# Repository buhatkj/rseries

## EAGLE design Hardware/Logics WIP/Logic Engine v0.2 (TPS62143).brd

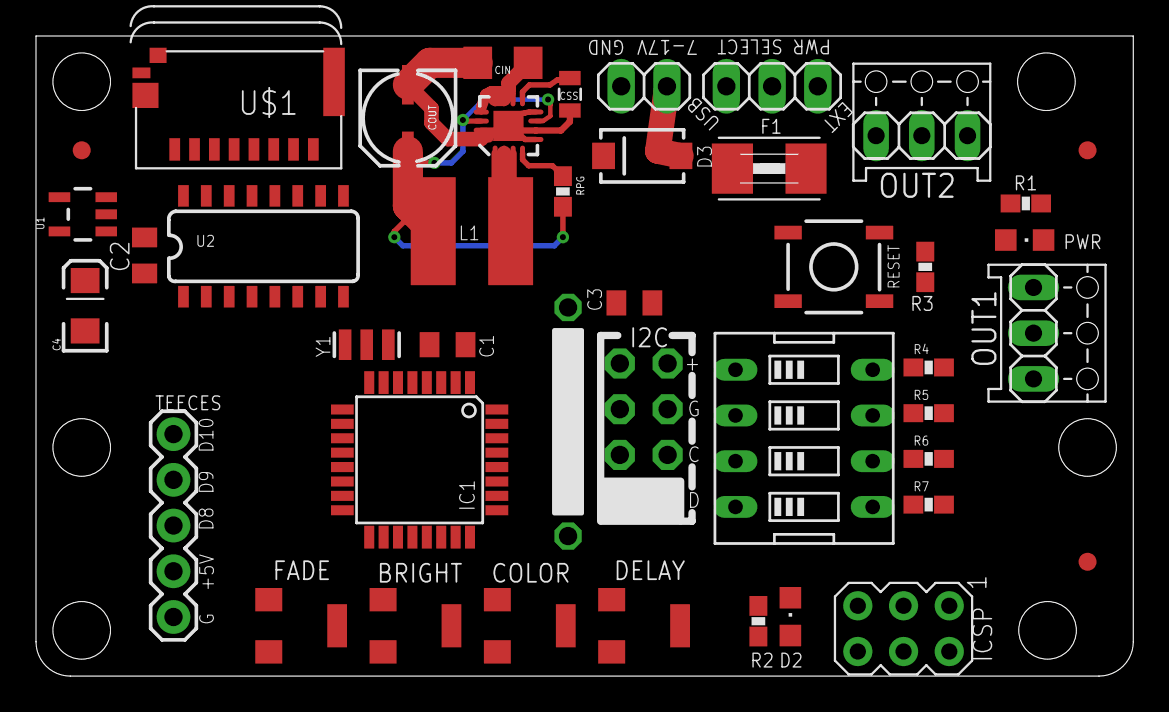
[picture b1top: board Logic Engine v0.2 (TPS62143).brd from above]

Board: 2 copper layers, 61.0 x 35.6 mm, 44 parts (0 on the bottom side), 44 nets.

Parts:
BRIGHT: 3364
C1, C2, C3: 0.1uF; C0805K
C4: 10uF; EIA3216
CIN: 1206
COLOR: 3364
COUT: PANASONIC_C
CSS: 0805
D2: CHIPLED_0805
D3: BA340LA; SMA-DIODE
DELAY: 3364
EXT_PWR: 1X02
F1: 1812
FADE: 3364
FID1, FID2, FID3: FIDUCIAL1X2.5; FIDUCIAL-1X2.5
FTDI: GRN TX RX 5V G BLK; 1X06-CLEAN
I2C, I2C1: 1X04-CB
IC1: MEGA328P; TQFP32-08
ICSP: AVRISP-6; AVRISP
L1: 33uH; SRN6045
OUT1, OUT2: MDF7_1X03
PWR: CHIPLED_0805
PWR_SEL1: 1X03
R1, R2: 1K; 0603-RES
R3, R4, R5, R6, R7: 10K; 0603-RES
RESET: TACTILE_SWITCH_SMD
RPG: 0603-RES
SW1: EDG-04
TEECES: 1X05
U1: V_REG_LDOSMD; SOT23-5
U2: HEX_CONVERTER; SO016
U3: TPS62143; QFN16-3X3MM_1:1_V03
U$1: MICROSD; MICROSD_SMALL
Y1: 16MHz; RESONATOR-SMD

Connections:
+5V: BRIGHT.3, C1.1, C2.1, COLOR.3, DELAY.3, F1.1, FADE.3, I2C.4, I2C1.4, IC1.4, IC1.6, IC1.18, ICSP.2, OUT1.2, OUT2.2, R1.1, R3.1, TEECES.2, U1.1, U1.3, U$1.4
ANALOG0: DELAY.2, IC1.23
ANALOG1: FADE.2, IC1.24
ANALOG2: BRIGHT.2, IC1.25
ANALOG3: COLOR.2, IC1.26
ANALOG4: I2C.1, I2C1.1, IC1.27
ANALOG5: I2C.2, I2C1.2, IC1.28
DIGITAL2: IC1.32, SW1.1
DIGITAL3: IC1.1, SW1.2
DIGITAL4: IC1.2, SW1.3
DIGITAL5: IC1.9, SW1.4
DIGITAL6: IC1.10, OUT1.1, OUT2.1
DIGITAL7: IC1.11, TEECES.5
DIGITAL8: IC1.12, TEECES.4
DIGITAL9: IC1.13, TEECES.3
DIGITAL10: IC1.14, U2.3
GND: BRIGHT.1, C1.2, C2.2, C4.C, CIN.2, COLOR.1, COUT.-, CSS.2, D2.C, DELAY.1, EXT_PWR.1, FADE.1, FTDI.1, FTDI.2, I2C.3, I2C1.3, IC1.3, IC1.5, IC1.21, ICSP.6, OUT1.3, OUT2.3, PWR.C, R4.2, R5.2, R6.2, R7.2, RESET.3, TEECES.1, U1.2, U2.8, U3.5, U3.6, U3.8, U3.15, U3.16, U3.EXT, U$1.6, U$1.MT1, U$1.MT2, Y1.2
MISO: IC1.16, ICSP.1, U$1.7
MOSI: IC1.15, ICSP.4, U2.5
unnamed: IC1.7, Y1.1
unnamed: IC1.8, Y1.3
unnamed: CIN.1, D3.C, U3.10, U3.11, U3.12, U3.13
unnamed: D2.A, R2.2
unnamed: PWR.A, R1.2
unnamed: COUT.+, L1.2, PWR_SEL1.1, RPG.2, U3.7, U3.14
unnamed: RPG.1, U3.4
unnamed: F1.2, PWR_SEL1.2
unnamed: D3.A, EXT_PWR.2
unnamed: R4.1, SW1.8
unnamed: R5.1, SW1.7
unnamed: R6.1, SW1.6
unnamed: R7.1, SW1.5
unnamed: U2.4, U$1.3
unnamed: U2.6, U$1.5
unnamed: U2.2, U$1.2
unnamed: C4.A, U1.5, U2.1
unnamed: CSS.1, U3.9
unnamed: L1.1, U3.1, U3.2, U3.3
RST: C3.2, IC1.29, ICSP.5, R3.2, RESET.1
RTS#: C3.1, FTDI.6
RXD: FTDI.4, IC1.30
SCK: IC1.17, ICSP.3, R2.1, U2.7
TXD: FTDI.5, IC1.31
USB_5V: FTDI.3, PWR_SEL1.3

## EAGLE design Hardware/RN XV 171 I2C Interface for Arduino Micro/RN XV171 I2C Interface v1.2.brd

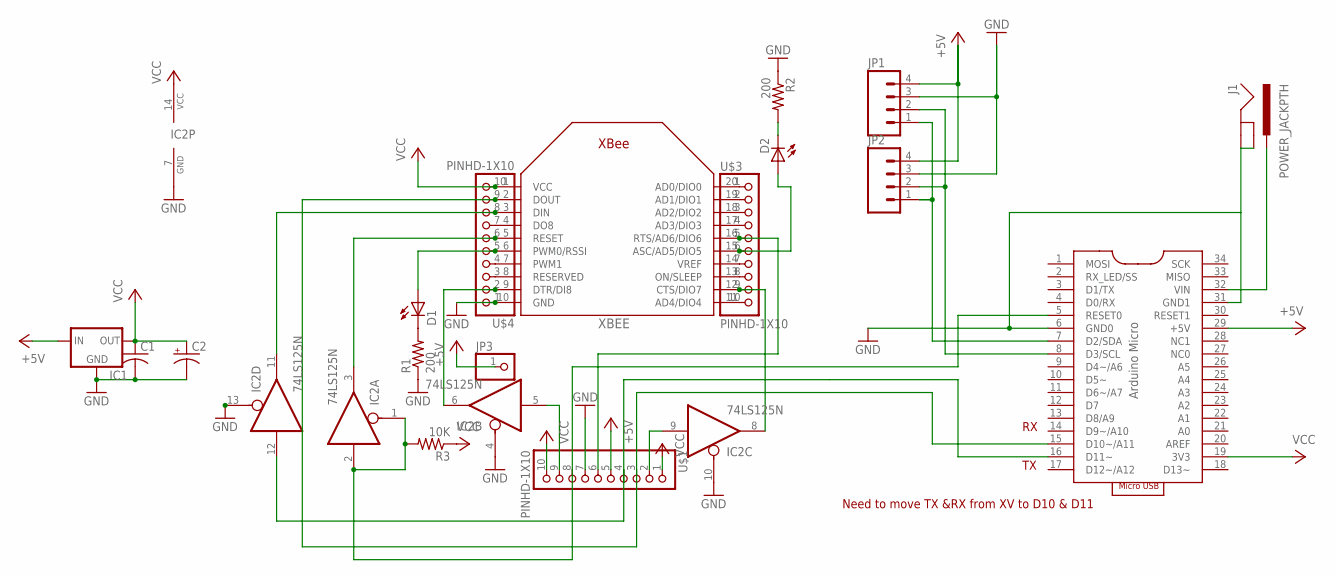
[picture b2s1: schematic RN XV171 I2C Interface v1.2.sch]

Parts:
C1: C-US025-025X050; C025-025X050
C2: CPOL-USE2.5-5; E2,5-5
D1, D2: LED3MM
IC1: MC1700; TO92
IC2: 74LS125N; DIL14
J1: POWER_JACKPTH; POWER_JACK_PTH
JP1, JP2: M041X04_NO_SILK; 1X04_NO_SILK
JP3: PINHD-1X1; 1X01
R1, R2: 200; 0207/10
R3: 10K; 0207/10
U$1, U$3, U$4: PINHD-1X10; 1X10-BIG
U$9: ARDUINO-MICRO; ARDUINO-MICRO-DIP34
XBEE: XBEE

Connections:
+5V: IC1.2 (IN), JP1.4, JP2.4, JP3.1, U$1.5, U$9.29 (+5V)
GND: C1.2, C2.-, IC1.1 (GND), IC2.4 (OE), IC2.7 (GND), IC2.10 (OE), IC2.13 (OE), J1.GND, J1.GNDBREAK, JP1.3, JP2.3, R1.1, R2.1, U$1.7, U$4.1, U$9.6 (GND0), U$9.31 (GND1), XBEE.10 (GND)
unnamed: IC2.12 (I), U$1.4, U$9.16 (D11~)
unnamed: IC2.11 (O), U$4.8, XBEE.3 (DIN)
unnamed: IC2.5 (I), U$1.9
unnamed: IC2.8 (O), U$3.9, XBEE.12 (CTS/DIO7)
unnamed: D2.K (C), R2.2
unnamed: U$4.7, XBEE.4 (DO8)
unnamed: D1.A, U$4.5, XBEE.6 (PWM0/RSSI)
unnamed: D1.K (C), R1.2
unnamed: D2.A, U$3.6, XBEE.15 (ASC/AD5/DIO5)
unnamed: IC2.6 (O), U$4.2, XBEE.9 (DTR/DI8)
unnamed: U$4.3, XBEE.8 (RESERVED)
unnamed: U$4.4, XBEE.7 (PWM1)
unnamed: IC2.3 (O), U$4.6, XBEE.5 (RESET)
unnamed: U$3.1, XBEE.20 (AD0/DIO0)
unnamed: U$3.2, XBEE.19 (AD1/DIO1)
unnamed: U$3.3, XBEE.18 (AD2/DIO2)
unnamed: U$3.4, XBEE.17 (AD3/DIO3)
unnamed: U$3.7, XBEE.14 (VREF)
unnamed: U$3.8, XBEE.13 (ON/SLEEP)
unnamed: U$3.10, XBEE.11 (AD4/DIO4)
unnamed: IC2.9 (I), U$1.2
unnamed: JP1.2, JP2.2, U$9.8 (D3/SCL)
unnamed: JP1.1, JP2.1, U$9.7 (D2/SDA)
unnamed: J1.PWR, U$9.32 (VIN)
RESET: IC2.1 (OE), IC2.2 (I), R3.2, U$1.8, U$9.5 (RESET0)
RTS: U$1.6, U$3.5, XBEE.16 (RTS/AD6/DIO6)
TX: U$1.3, U$4.9, U$9.15 (D10~/A11), XBEE.2 (DOUT)
VCC: C1.1, C2.+, IC1.3 (OUT), IC2.14 (VCC), R3.1, U$1.1, U$1.10, U$4.10, U$9.19 (3V3), XBEE.1 (VCC)

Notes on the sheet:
Need to move TX &RX from XV to D10 & D11

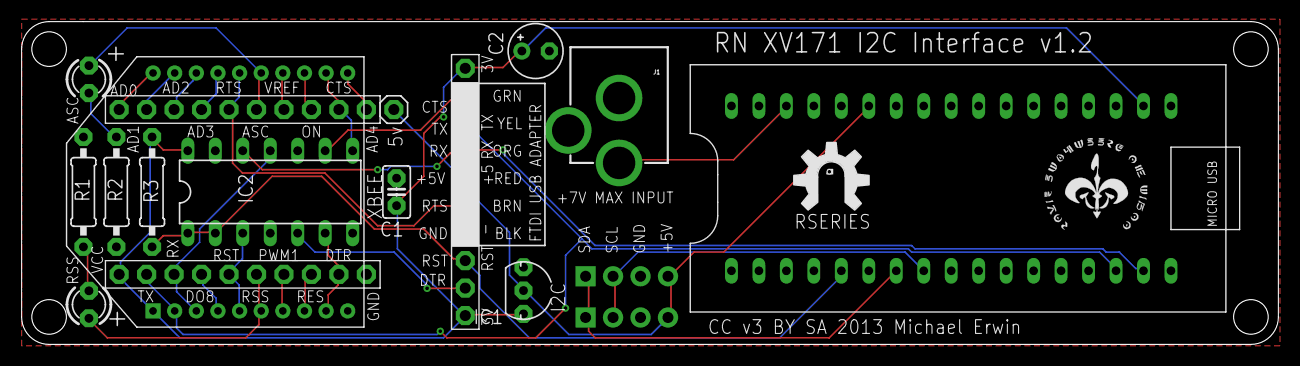
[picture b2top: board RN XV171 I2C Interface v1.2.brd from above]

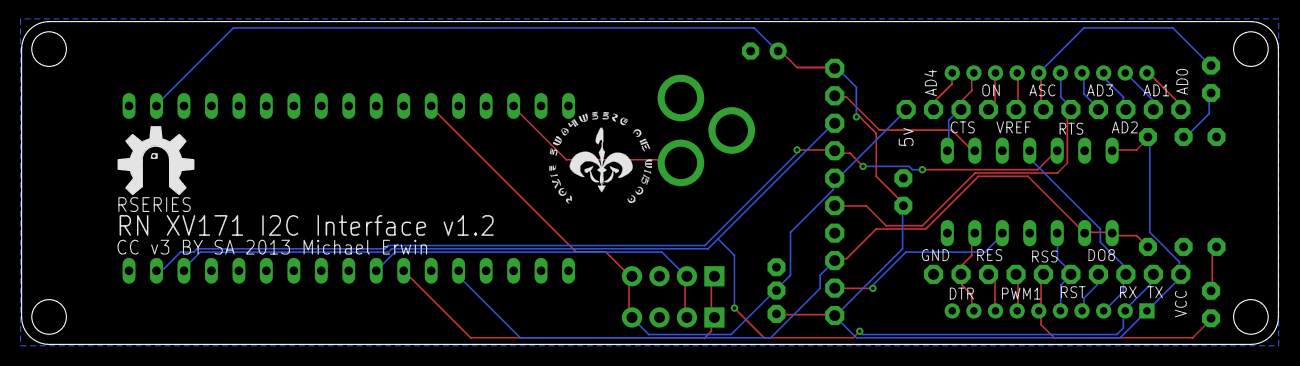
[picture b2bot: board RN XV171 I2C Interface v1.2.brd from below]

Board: 2 copper layers, 116.2 x 29.8 mm, 22 parts (2 on the bottom side), 30 nets.

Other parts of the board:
U$2, U$8: RSERIES-OSHW-LOGO-LARGE
U$5, U$7: ROYAL-ENGINEERS-OF-NABOO-SMALL

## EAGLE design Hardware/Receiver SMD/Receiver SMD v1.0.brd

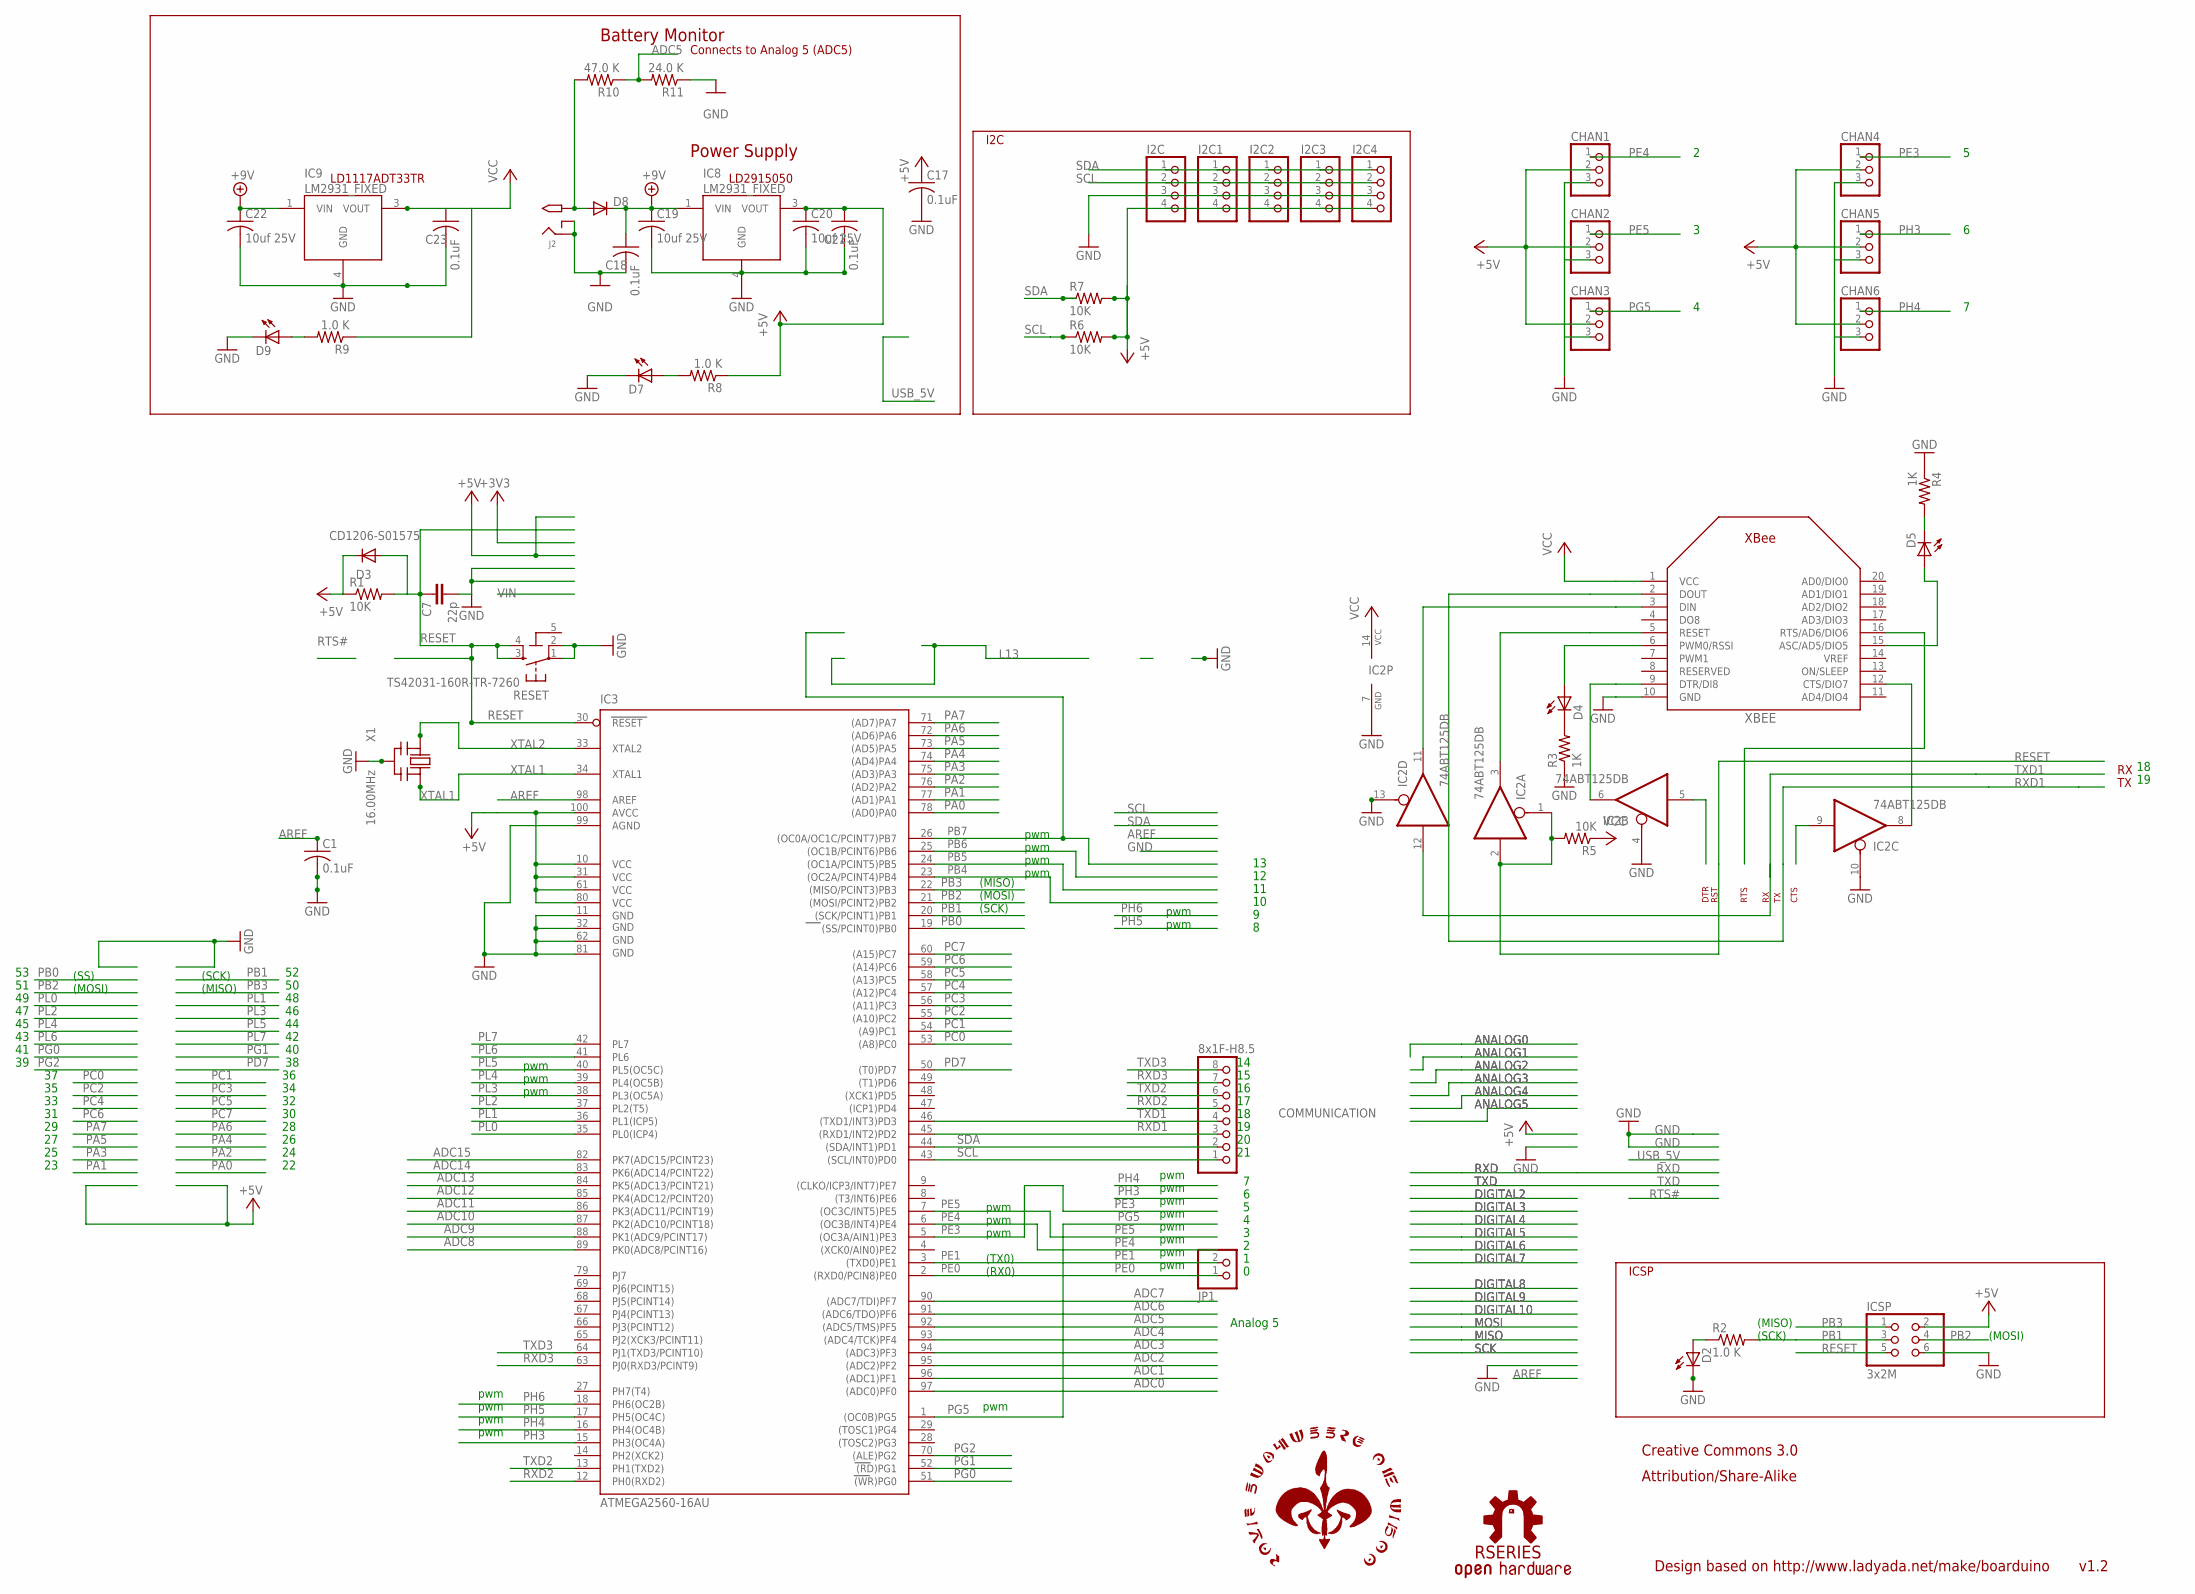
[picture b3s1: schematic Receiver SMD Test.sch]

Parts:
C1, C17, C18, C21, C23: 0.1uF; C1206K
C7: 22p; C1206K
C19, C20, C22: 10uf 25V; C1206K
CHAN1, CHAN2, CHAN3, CHAN4, CHAN5, CHAN6: PINHD-1X3; 1X03
COMMUNICATION: 8x1F-H8.5; 1X08
D2: RED; CHIPLED_1206
D3: CD1206-S01575; MINIMELF
D4, D5, D7, D9: LEDCHIPLED_1206; CHIPLED_1206
D8: DIODE-SMB; SMB
I2C, I2C1, I2C2, I2C3, I2C4: PINHD-1X4CB; 1X04-CB
IC2: 74ABT125DB; SSOP14
IC3: ATMEGA2560-16AU; TQFP100
IC8, IC9: LM2931_FIXED; DPAK
ICSP: 3x2M; 2X03
J2: 2.1MMJACK; PJ-102A
JP1: PINHD-1X2; 1X02
R1, R5, R6, R7: 10K; R1206
R2, R8, R9: 1.0 K; M1206
R3, R4: 1K; R1206
R10: 47.0 K; M1206
R11: 24.0 K; M1206
RESET: TS42031-160R-TR-7260; TS42
U$1: ROYAL-ENGINEERS-OF-NABOO
U$3: RSERIES-OSHW-LOGO; RSERIES-OSHW-LOGO-LARGE
X1: 16.00MHz; CERM_OSC
XBEE: XBEE

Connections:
5-GND: RESET.5 (5-GND)
+5V: C17.1, C20.1, C21.1, CHAN1.2, CHAN2.2, CHAN3.2, CHAN4.2, CHAN5.2, CHAN6.2, D3.C, I2C.4, I2C1.4, I2C2.4, I2C3.4, I2C4.4, IC3.10 (VCC), IC3.31 (VCC1), IC3.61 (VCC2), IC3.80 (VCC3), IC3.100 (AVCC), IC8.3 (VOUT), ICSP.2, R1.1, R6.2, R7.2, R8.1
+9V: C18.1, C19.1, C22.1, D8.C, IC8.1 (VIN), IC9.1 (VIN)
ADC0: IC3.97 ((ADC0)PF0)
ADC1: IC3.96 ((ADC1)PF1)
ADC2: IC3.95 ((ADC2)PF2)
ADC3: IC3.94 ((ADC3)PF3)
ADC4: IC3.93 ((ADC4/TCK)PF4)
ADC5: IC3.92 ((ADC5/TMS)PF5), R10.1, R11.2
ADC6: IC3.91 ((ADC6/TDO)PF6)
ADC7: IC3.90 ((ADC7/TDI)PF7)
ADC8: IC3.89 (PK0(ADC8/PCINT16))
ADC9: IC3.88 (PK1(ADC9/PCINT17))
ADC10: IC3.87 (PK2(ADC10/PCINT18))
ADC11: IC3.86 (PK3(ADC11/PCINT19))
ADC12: IC3.85 (PK4(ADC12/PCINT20))
ADC13: IC3.84 (PK5(ADC13/PCINT21))
ADC14: IC3.83 (PK6(ADC14/PCINT22))
ADC15: IC3.82 (PK7(ADC15/PCINT23))
AREF: C1.1, IC3.98 (AREF)
GND: C1.2, C7.2, C17.2, C18.2, C22.2, C23.2, CHAN1.3, CHAN2.3, CHAN3.3, CHAN4.3, CHAN5.3, CHAN6.3, D2.C, D7.C, D9.C, I2C.3, I2C1.3, I2C2.3, I2C3.3, I2C4.3, IC2.4 (OE), IC2.7 (GND), IC2.10 (OE), IC2.13 (OE), IC3.11 (GND), IC3.32 (GND1), IC3.62 (GND2), IC3.81 (GND3), IC3.99 (AGND), IC8.4 (GND), IC9.4 (GND), ICSP.6, J2.RING, J2.RING_SW, R3.1, R4.1, R11.1, RESET.1, RESET.2, X1.P$2 (GND), XBEE.10 (GND)
unnamed: IC2.11 (O), XBEE.3 (DIN)
unnamed: D5.C, R4.2
unnamed: D4.A, XBEE.6 (PWM0/RSSI)
unnamed: D4.C, R3.2
unnamed: D9.A, R9.2
unnamed: IC2.6 (O), XBEE.9 (DTR/DI8)
unnamed: D2.A, R2.1
unnamed: IC2.3 (O), XBEE.5 (RESET)
unnamed: IC2.8 (O), XBEE.12 (CTS/DIO7)
unnamed: D5.A, XBEE.15 (ASC/AD5/DIO5)
unnamed: D7.A, R8.2
unnamed: D8.A, J2.TIP, R10.2
unnamed: C19.2, C20.2, C21.2
PA0: IC3.78 ((AD0)PA0)
PA1: IC3.77 ((AD1)PA1)
PA2: IC3.76 ((AD2)PA2)
PA3: IC3.75 ((AD3)PA3)
PA4: IC3.74 ((AD4)PA4)
PA5: IC3.73 ((AD5)PA5)
PA6: IC3.72 ((AD6)PA6)
PA7: IC3.71 ((AD7)PA7)
PB0: IC3.19 ((SS/PCINT0)PB0)
PB1: IC3.20 ((SCK/PCINT1)PB1), ICSP.3, R2.2
PB2: IC3.21 ((MOSI/PCINT2)PB2), ICSP.4
PB3: IC3.22 ((MISO/PCINT3)PB3), ICSP.1
PB4: IC3.23 ((OC2A/PCINT4)PB4)
PB5: IC3.24 ((OC1A/PCINT5)PB5)
PB6: IC3.25 ((OC1B/PCINT6)PB6)
PB7: IC3.26 ((OC0A/OC1C/PCINT7)PB7)
PC0: IC3.53 ((A8)PC0)
PC1: IC3.54 ((A9)PC1)
PC2: IC3.55 ((A10)PC2)
PC3: IC3.56 ((A11)PC3)
PC4: IC3.57 ((A12)PC4)
PC5: IC3.58 ((A13)PC5)
PC6: IC3.59 ((A14)PC6)
PC7: IC3.60 ((A15)PC7)
PD7: IC3.50 ((T0)PD7)
PE0: IC3.2 ((RXD0/PCIN8)PE0), JP1.1
PE1: IC3.3 ((TXD0)PE1), JP1.2
PE3: CHAN4.1, IC3.5 ((OC3A/AIN1)PE3)
PE4: CHAN1.1, IC3.6 ((OC3B/INT4)PE4)
PE5: CHAN2.1, IC3.7 ((OC3C/INT5)PE5)
PG0: IC3.51 ((WR)PG0)
PG1: IC3.52 ((RD)PG1)
PG2: IC3.70 ((ALE)PG2)
PG5: CHAN3.1, IC3.1 ((OC0B)PG5)
PH3: CHAN5.1, IC3.15 (PH3(OC4A))
PH4: CHAN6.1, IC3.16 (PH4(OC4B))
PH5: IC3.17 (PH5(OC4C))
PH6: IC3.18 (PH6(OC2B))
PL0: IC3.35 (PL0(ICP4))
PL1: IC3.36 (PL1(ICP5))
PL2: IC3.37 (PL2(T5))
PL3: IC3.38 (PL3(OC5A))
PL4: IC3.39 (PL4(OC5B))
PL5: IC3.40 (PL5(OC5C))
PL6: IC3.41 (PL6)
PL7: IC3.42 (PL7)
RESET: C7.1, D3.A, IC2.1 (OE), IC2.2 (I), IC3.30 (RESET), ICSP.5, R1.2, R5.2, RESET.3, RESET.4
RTS: XBEE.16 (RTS/AD6/DIO6)
RXD1: COMMUNICATION.3, IC3.45 ((RXD1/INT2)PD2), XBEE.2 (DOUT)
RXD2: COMMUNICATION.5, IC3.12 (PH0(RXD2))
RXD3: COMMUNICATION.7, IC3.63 (PJ0(RXD3/PCINT9))
SCL: COMMUNICATION.1, I2C.2, I2C1.2, I2C2.2, I2C3.2, I2C4.2, IC3.43 ((SCL/INT0)PD0), R6.1
SDA: COMMUNICATION.2, I2C.1, I2C1.1, I2C2.1, I2C3.1, I2C4.1, IC3.44 ((SDA/INT1)PD1), R7.1
TXD1: COMMUNICATION.4, IC2.12 (I), IC3.46 ((TXD1/INT3)PD3)
TXD2: COMMUNICATION.6, IC3.13 (PH1(TXD2))
TXD3: COMMUNICATION.8, IC3.64 (PJ1(TXD3/PCINT10))
VCC: C23.1, IC2.14 (VCC), IC9.3 (VOUT), R5.1, R9.1, XBEE.1 (VCC)
XTAL1: IC3.34 (XTAL1), X1.P$3 (OUT)
XTAL2: IC3.33 (XTAL2), X1.P$1 (IN)

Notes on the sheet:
(SCK)
(MISO)
(MOSI)
pwm
(TX0)
(RX0)
(SS)
DTR
RST
RTS
CTS
v1.2
Design based on http://www.ladyada.net/make/boarduino
Creative Commons 3.0
Attribution/Share-Alike
I2C
ICSP
Power Supply
LD2915050
LD1117ADT33TR
Battery Monitor
Analog 5
Connects to Analog 5 (ADC5)

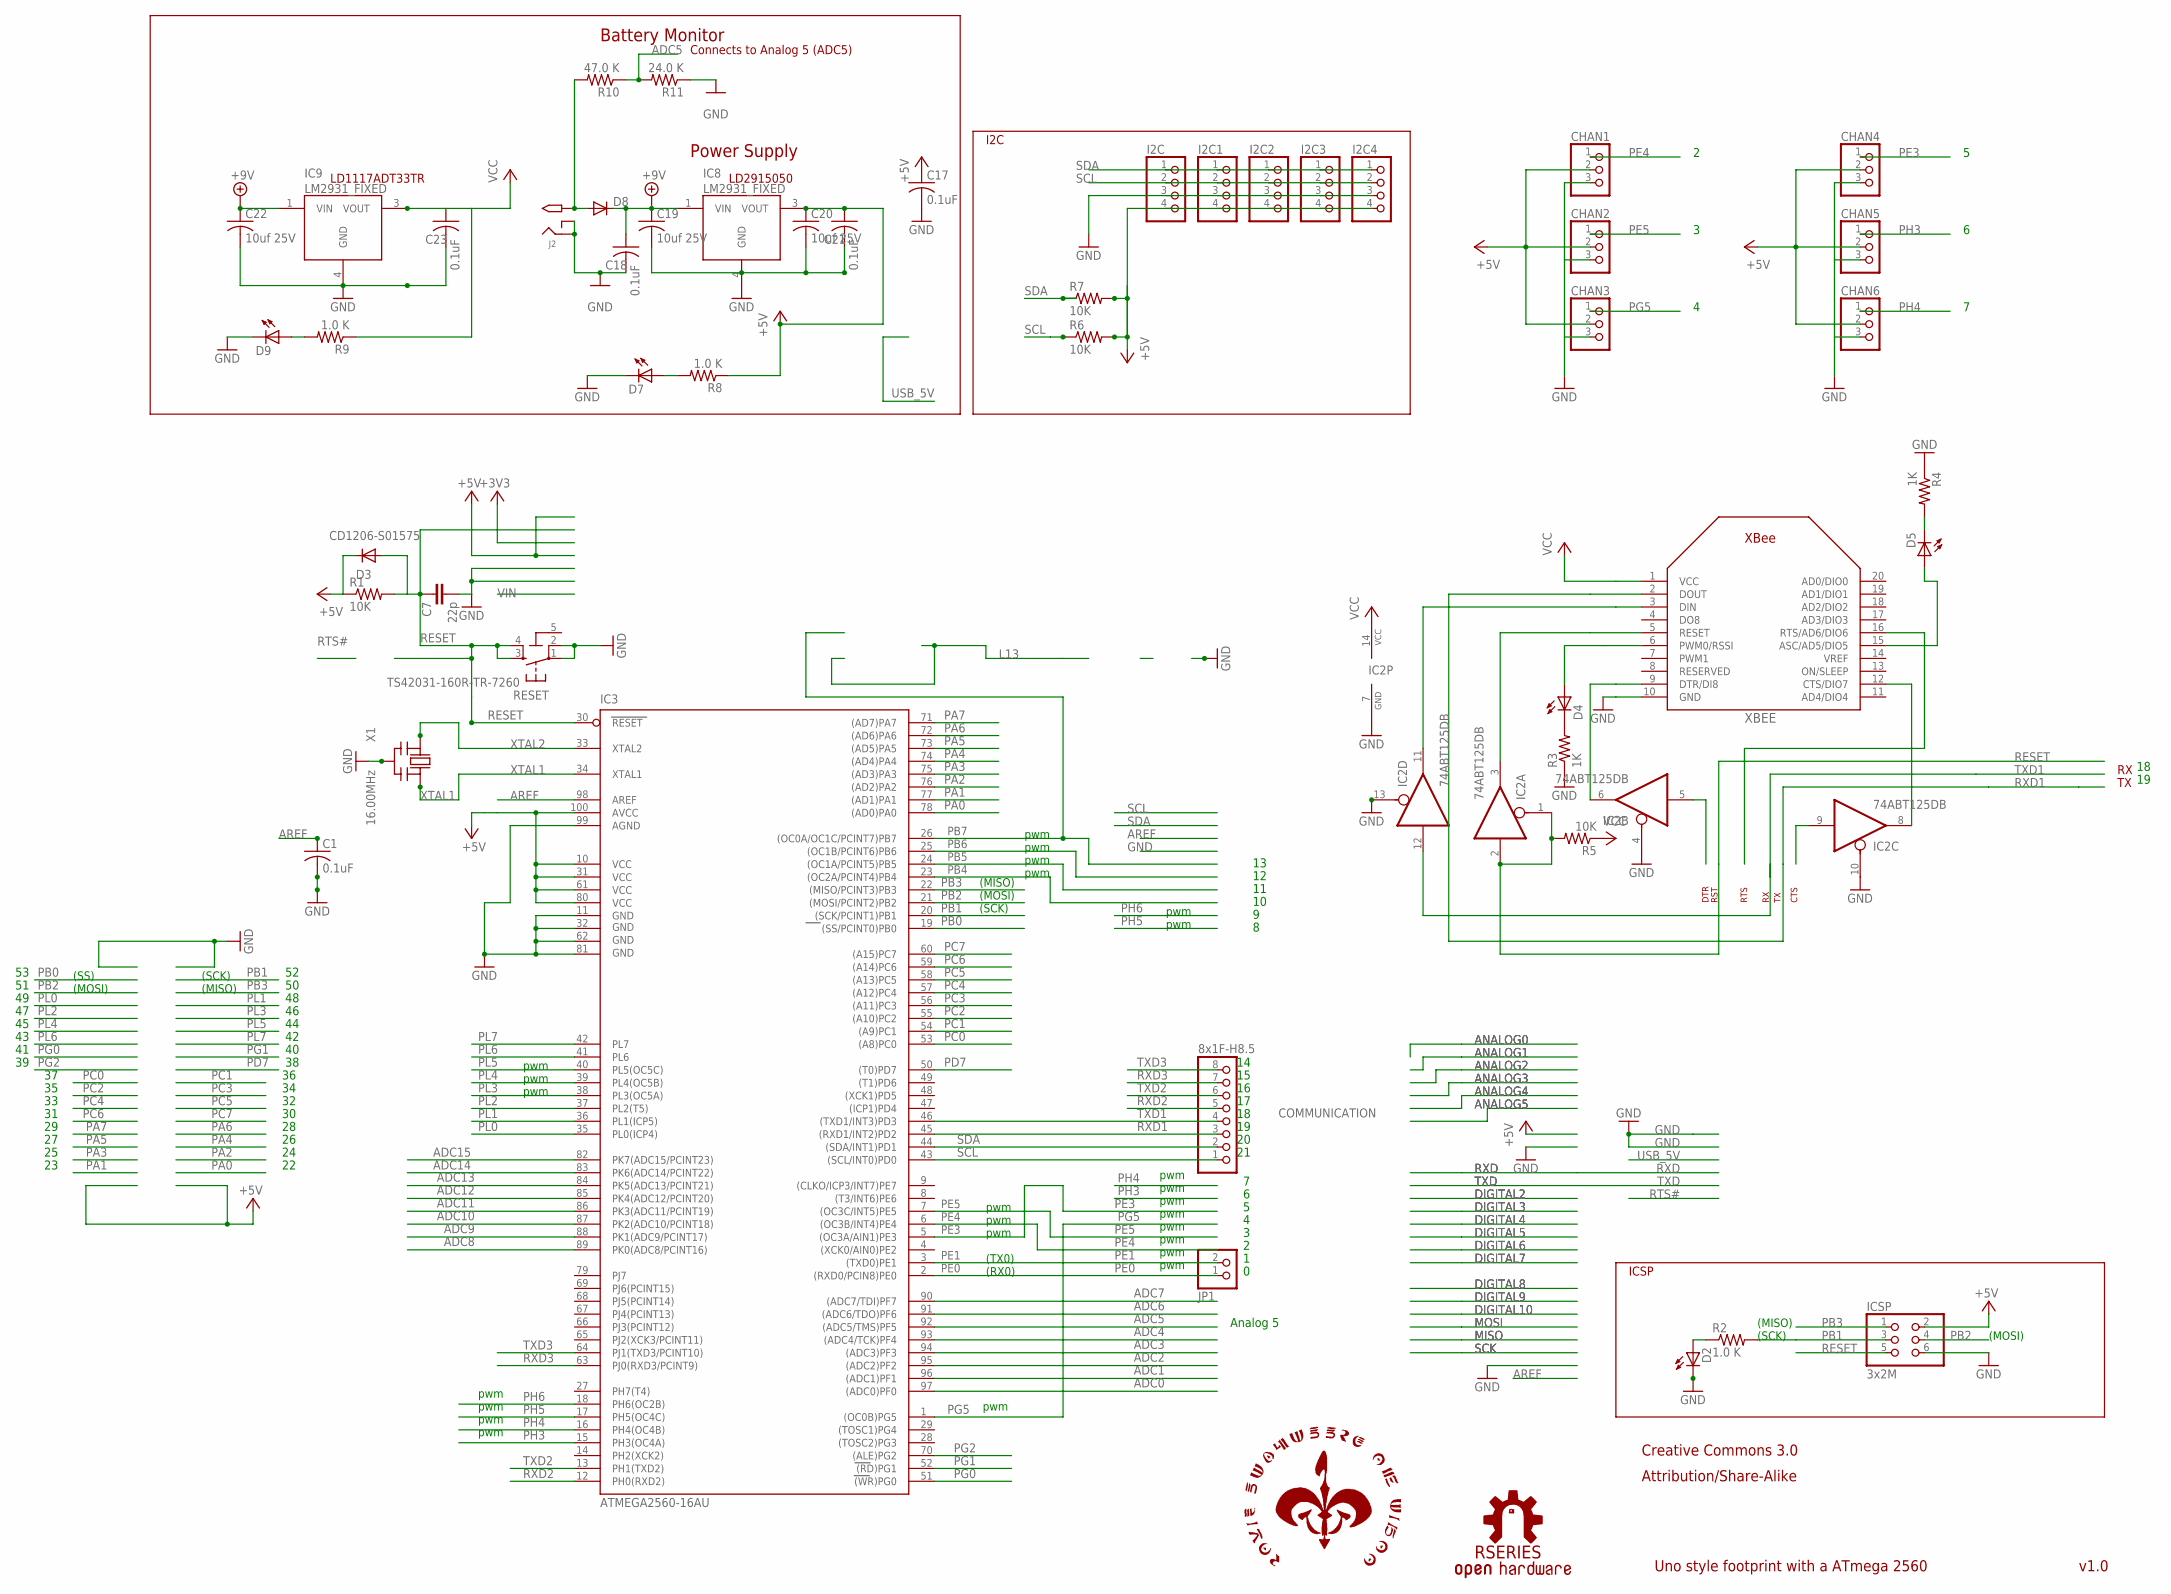
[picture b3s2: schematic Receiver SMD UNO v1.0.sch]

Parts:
C1, C17, C18, C21, C23: 0.1uF; C1206K
C7: 22p; C1206K
C19, C20, C22: 10uf 25V; C1206K
CHAN1, CHAN2, CHAN3, CHAN4, CHAN5, CHAN6: PINHD-1X3; 1X03
COMMUNICATION: 8x1F-H8.5; 1X08
D2: RED; CHIPLED_1206
D3: CD1206-S01575; MINIMELF
D4, D5, D7, D9: LEDCHIPLED_1206; CHIPLED_1206
D8: DIODE-SMB; SMB
I2C, I2C1, I2C2, I2C3, I2C4: PINHD-1X4CB; 1X04-CB
IC2: 74ABT125DB; SSOP14
IC3: ATMEGA2560-16AU; TQFP100
IC8, IC9: LM2931_FIXED; DPAK
ICSP: 3x2M; 2X03
J2: 2.1MMJACK; PJ-102A
JP1: PINHD-1X2; 1X02
R1, R5, R6, R7: 10K; R1206
R2, R8, R9: 1.0 K; M1206
R3, R4: 1K; R1206
R10: 47.0 K; M1206
R11: 24.0 K; M1206
RESET: TS42031-160R-TR-7260; TS42
U$1: ROYAL-ENGINEERS-OF-NABOO
U$3: RSERIES-OSHW-LOGO; RSERIES-OSHW-LOGO-LARGE
X1: 16.00MHz; CERM_OSC
XBEE: XBEE

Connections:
5-GND: RESET.5 (5-GND)
+5V: C17.1, C20.1, C21.1, CHAN1.2, CHAN2.2, CHAN3.2, CHAN4.2, CHAN5.2, CHAN6.2, D3.C, I2C.4, I2C1.4, I2C2.4, I2C3.4, I2C4.4, IC3.10 (VCC), IC3.31 (VCC1), IC3.61 (VCC2), IC3.80 (VCC3), IC3.100 (AVCC), IC8.3 (VOUT), ICSP.2, R1.1, R6.2, R7.2, R8.1
+9V: C18.1, C19.1, C22.1, D8.C, IC8.1 (VIN), IC9.1 (VIN)
ADC0: IC3.97 ((ADC0)PF0)
ADC1: IC3.96 ((ADC1)PF1)
ADC2: IC3.95 ((ADC2)PF2)
ADC3: IC3.94 ((ADC3)PF3)
ADC4: IC3.93 ((ADC4/TCK)PF4)
ADC5: IC3.92 ((ADC5/TMS)PF5), R10.1, R11.2
ADC6: IC3.91 ((ADC6/TDO)PF6)
ADC7: IC3.90 ((ADC7/TDI)PF7)
ADC8: IC3.89 (PK0(ADC8/PCINT16))
ADC9: IC3.88 (PK1(ADC9/PCINT17))
ADC10: IC3.87 (PK2(ADC10/PCINT18))
ADC11: IC3.86 (PK3(ADC11/PCINT19))
ADC12: IC3.85 (PK4(ADC12/PCINT20))
ADC13: IC3.84 (PK5(ADC13/PCINT21))
ADC14: IC3.83 (PK6(ADC14/PCINT22))
ADC15: IC3.82 (PK7(ADC15/PCINT23))
AREF: C1.1, IC3.98 (AREF)
GND: C1.2, C7.2, C17.2, C18.2, C22.2, C23.2, CHAN1.3, CHAN2.3, CHAN3.3, CHAN4.3, CHAN5.3, CHAN6.3, D2.C, D7.C, D9.C, I2C.3, I2C1.3, I2C2.3, I2C3.3, I2C4.3, IC2.4 (OE), IC2.7 (GND), IC2.10 (OE), IC2.13 (OE), IC3.11 (GND), IC3.32 (GND1), IC3.62 (GND2), IC3.81 (GND3), IC3.99 (AGND), IC8.4 (GND), IC9.4 (GND), ICSP.6, J2.RING, J2.RING_SW, R3.1, R4.1, R11.1, RESET.1, RESET.2, X1.P$2 (GND), XBEE.10 (GND)
unnamed: IC2.11 (O), XBEE.3 (DIN)
unnamed: D5.C, R4.2
unnamed: D4.A, XBEE.6 (PWM0/RSSI)
unnamed: D4.C, R3.2
unnamed: D9.A, R9.2
unnamed: IC2.6 (O), XBEE.9 (DTR/DI8)
unnamed: D2.A, R2.1
unnamed: IC2.3 (O), XBEE.5 (RESET)
unnamed: IC2.8 (O), XBEE.12 (CTS/DIO7)
unnamed: D5.A, XBEE.15 (ASC/AD5/DIO5)
unnamed: D7.A, R8.2
unnamed: D8.A, J2.TIP, R10.2
unnamed: C19.2, C20.2, C21.2
PA0: IC3.78 ((AD0)PA0)
PA1: IC3.77 ((AD1)PA1)
PA2: IC3.76 ((AD2)PA2)
PA3: IC3.75 ((AD3)PA3)
PA4: IC3.74 ((AD4)PA4)
PA5: IC3.73 ((AD5)PA5)
PA6: IC3.72 ((AD6)PA6)
PA7: IC3.71 ((AD7)PA7)
PB0: IC3.19 ((SS/PCINT0)PB0)
PB1: IC3.20 ((SCK/PCINT1)PB1), ICSP.3, R2.2
PB2: IC3.21 ((MOSI/PCINT2)PB2), ICSP.4
PB3: IC3.22 ((MISO/PCINT3)PB3), ICSP.1
PB4: IC3.23 ((OC2A/PCINT4)PB4)
PB5: IC3.24 ((OC1A/PCINT5)PB5)
PB6: IC3.25 ((OC1B/PCINT6)PB6)
PB7: IC3.26 ((OC0A/OC1C/PCINT7)PB7)
PC0: IC3.53 ((A8)PC0)
PC1: IC3.54 ((A9)PC1)
PC2: IC3.55 ((A10)PC2)
PC3: IC3.56 ((A11)PC3)
PC4: IC3.57 ((A12)PC4)
PC5: IC3.58 ((A13)PC5)
PC6: IC3.59 ((A14)PC6)
PC7: IC3.60 ((A15)PC7)
PD7: IC3.50 ((T0)PD7)
PE0: IC3.2 ((RXD0/PCIN8)PE0), JP1.1
PE1: IC3.3 ((TXD0)PE1), JP1.2
PE3: CHAN4.1, IC3.5 ((OC3A/AIN1)PE3)
PE4: CHAN1.1, IC3.6 ((OC3B/INT4)PE4)
PE5: CHAN2.1, IC3.7 ((OC3C/INT5)PE5)
PG0: IC3.51 ((WR)PG0)
PG1: IC3.52 ((RD)PG1)
PG2: IC3.70 ((ALE)PG2)
PG5: CHAN3.1, IC3.1 ((OC0B)PG5)
PH3: CHAN5.1, IC3.15 (PH3(OC4A))
PH4: CHAN6.1, IC3.16 (PH4(OC4B))
PH5: IC3.17 (PH5(OC4C))
PH6: IC3.18 (PH6(OC2B))
PL0: IC3.35 (PL0(ICP4))
PL1: IC3.36 (PL1(ICP5))
PL2: IC3.37 (PL2(T5))
PL3: IC3.38 (PL3(OC5A))
PL4: IC3.39 (PL4(OC5B))
PL5: IC3.40 (PL5(OC5C))
PL6: IC3.41 (PL6)
PL7: IC3.42 (PL7)
RESET: C7.1, D3.A, IC2.1 (OE), IC2.2 (I), IC3.30 (RESET), ICSP.5, R1.2, R5.2, RESET.3, RESET.4
RTS: XBEE.16 (RTS/AD6/DIO6)
RXD1: COMMUNICATION.3, IC3.45 ((RXD1/INT2)PD2), XBEE.2 (DOUT)
RXD2: COMMUNICATION.5, IC3.12 (PH0(RXD2))
RXD3: COMMUNICATION.7, IC3.63 (PJ0(RXD3/PCINT9))
SCL: COMMUNICATION.1, I2C.2, I2C1.2, I2C2.2, I2C3.2, I2C4.2, IC3.43 ((SCL/INT0)PD0), R6.1
SDA: COMMUNICATION.2, I2C.1, I2C1.1, I2C2.1, I2C3.1, I2C4.1, IC3.44 ((SDA/INT1)PD1), R7.1
TXD1: COMMUNICATION.4, IC2.12 (I), IC3.46 ((TXD1/INT3)PD3)
TXD2: COMMUNICATION.6, IC3.13 (PH1(TXD2))
TXD3: COMMUNICATION.8, IC3.64 (PJ1(TXD3/PCINT10))
VCC: C23.1, IC2.14 (VCC), IC9.3 (VOUT), R5.1, R9.1, XBEE.1 (VCC)
XTAL1: IC3.34 (XTAL1), X1.P$3 (OUT)
XTAL2: IC3.33 (XTAL2), X1.P$1 (IN)

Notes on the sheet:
(SCK)
(MISO)
(MOSI)
pwm
(TX0)
(RX0)
(SS)
DTR
RST
RTS
CTS
v1.0
Uno style footprint with a ATmega 2560
Creative Commons 3.0
Attribution/Share-Alike
I2C
ICSP
Power Supply
LD2915050
LD1117ADT33TR
Battery Monitor
Analog 5
Connects to Analog 5 (ADC5)

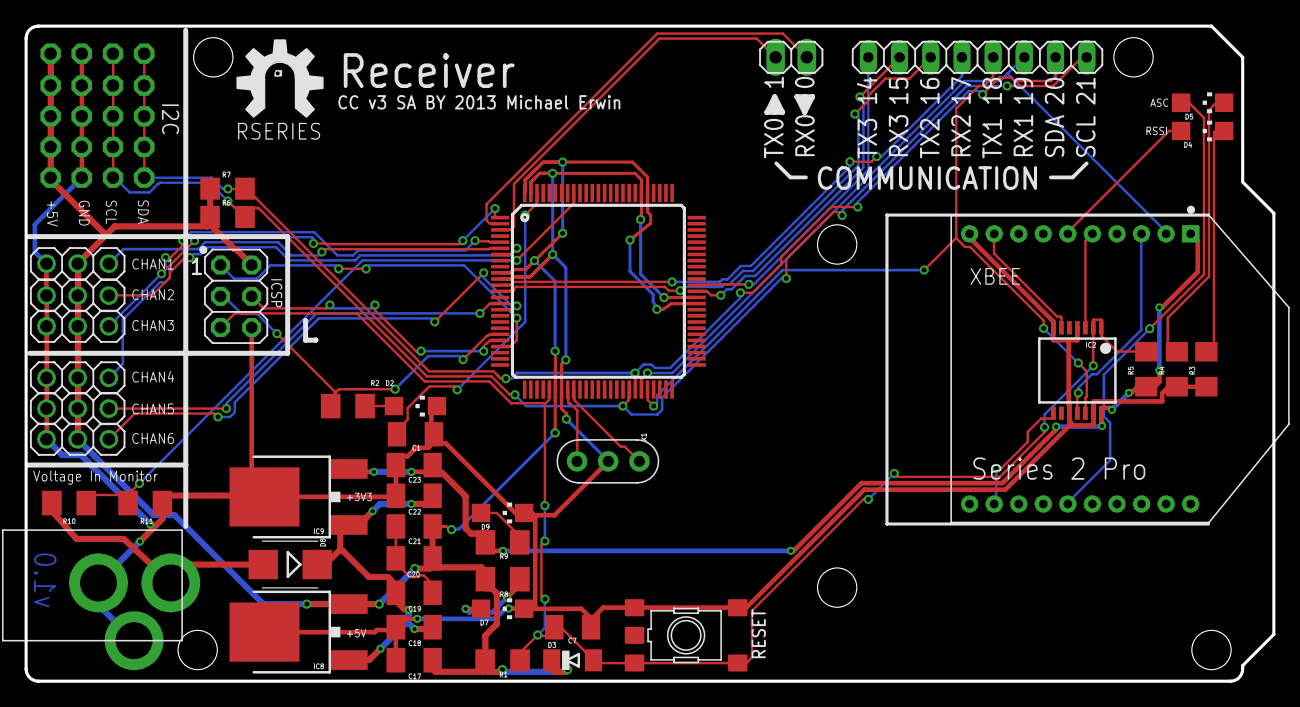
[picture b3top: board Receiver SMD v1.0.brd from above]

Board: 2 copper layers, 101.6 x 53.3 mm, 51 parts (1 on the bottom side), 41 nets.

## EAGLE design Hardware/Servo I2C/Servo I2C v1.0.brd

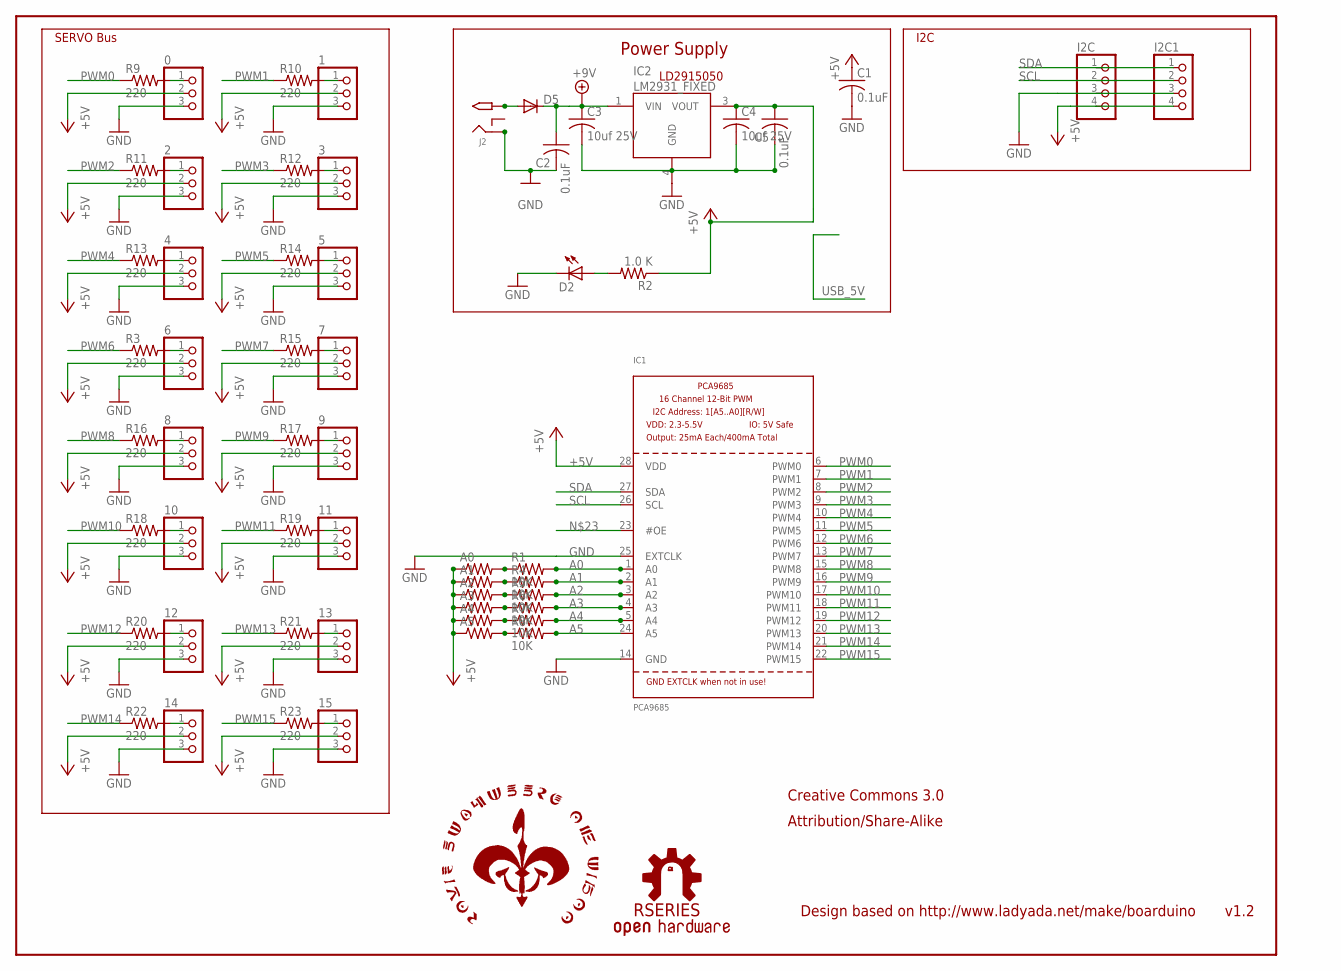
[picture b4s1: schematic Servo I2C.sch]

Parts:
0, 1, 2, 3, 4, 5, 6, 7, 8, 9, 10, 11, 12, 13, 14, 15: PINHD-1X3; 1X03
A0, A1, A2, A3, A4, A5: R-US_R0805; R0805
C1, C2, C5: 0.1uF; C1206K
C3, C4: 10uf 25V; C1206K
D2: LEDCHIPLED_1206; CHIPLED_1206
D5: DIODE-SMB; SMB
I2C, I2C1: PINHD-1X4CB; 1X04-CB
IC1: PCA9685; TSSOP28
IC2: LM2931_FIXED; DPAK
J2: 2.1MMJACK; PJ-102A
R1, R4, R5, R6, R7, R8: 10K; R0805
R2: 1.0 K; M1206
R3, R9, R10, R11, R12, R13, R14, R15, R16, R17, R18, R19, R20, R21, R22, R23: 220; R0805
U$2: RSERIES-OSHW-LOGOMEDIUM; RSERIES-OSHW-LOGO-MEDIUM
U$3: ROYAL-ENGINEERS-OF-NABOOSMALL; ROYAL-ENGINEERS-OF-NABOO-SMALL

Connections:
+5V: 0.2, 1.2, 2.2, 3.2, 4.2, 5.2, 6.2, 7.2, 8.2, 9.2, 10.2, 11.2, 12.2, 13.2, 14.2, 15.2, A0.1, A1.1, A2.1, A3.1, A4.1, A5.1, C1.1, C4.1, C5.1, I2C.4, I2C1.4, IC1.28 (VDD), IC2.3 (VOUT), R2.1
+9V: C2.1, C3.1, D5.C, IC2.1 (VIN)
A0: IC1.1 (A0), R1.2
A1: IC1.2 (A1), R4.2
A2: IC1.3 (A2), R5.2
A3: IC1.4 (A3), R6.2
A4: IC1.5 (A4), R7.2
A5: IC1.24 (A5), R8.2
GND: 0.3, 1.3, 2.3, 3.3, 4.3, 5.3, 6.3, 7.3, 8.3, 9.3, 10.3, 11.3, 12.3, 13.3, 14.3, 15.3, C1.2, C2.2, D2.C, I2C.3, I2C1.3, IC1.14 (GND), IC1.25 (EXTCLK), IC2.4 (GND), J2.RING
unnamed: A0.2, R1.1
unnamed: A1.2, R4.1
unnamed: A2.2, R5.1
unnamed: 6.1, R3.2
unnamed: D2.A, R2.2
unnamed: D5.A, J2.TIP
unnamed: A3.2, R6.1
unnamed: C3.2, C4.2, C5.2
unnamed: A4.2, R7.1
unnamed: A5.2, R8.1
unnamed: 1.1, R10.2
unnamed: 2.1, R11.2
unnamed: 3.1, R12.2
unnamed: 4.1, R13.2
unnamed: 5.1, R14.2
unnamed: 7.1, R15.2
unnamed: 8.1, R16.2
unnamed: 9.1, R17.2
unnamed: 10.1, R18.2
unnamed: 11.1, R19.2
unnamed: 12.1, R20.2
unnamed: 13.1, R21.2
unnamed: 14.1, R22.2
unnamed: 15.1, R23.2
unnamed: 0.1, R9.2
PWM0: IC1.6 (PWM0), R9.1
PWM1: IC1.7 (PWM1), R10.1
PWM2: IC1.8 (PWM2), R11.1
PWM3: IC1.9 (PWM3), R12.1
PWM4: IC1.10 (PWM4), R13.1
PWM5: IC1.11 (PWM5), R14.1
PWM6: IC1.12 (PWM6), R3.1
PWM7: IC1.13 (PWM7), R15.1
PWM8: IC1.15 (PWM8), R16.1
PWM9: IC1.16 (PWM9), R17.1
PWM10: IC1.17 (PWM10), R18.1
PWM11: IC1.18 (PWM11), R19.1
PWM12: IC1.19 (PWM12), R20.1
PWM13: IC1.20 (PWM13), R21.1
PWM14: IC1.21 (PWM14), R22.1
PWM15: IC1.22 (PWM15), R23.1
SCL: I2C.2, I2C1.2, IC1.26 (SCL)
SDA: I2C.1, I2C1.1, IC1.27 (SDA)

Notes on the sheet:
v1.2
Design based on http://www.ladyada.net/make/boarduino
Creative Commons 3.0
Attribution/Share-Alike
SERVO Bus
I2C
Power Supply
LD2915050

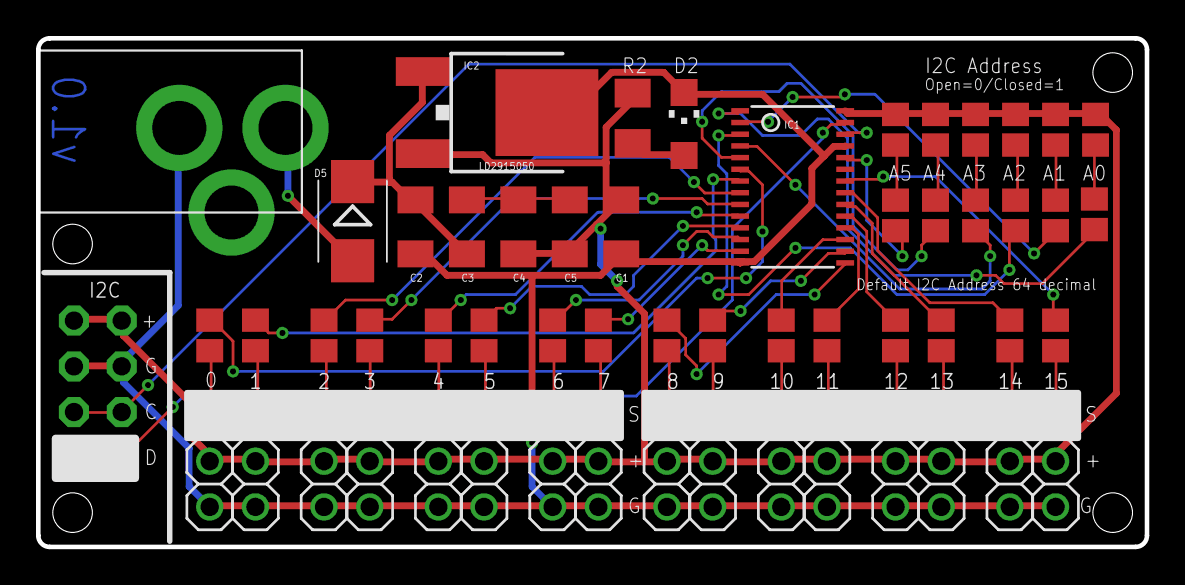
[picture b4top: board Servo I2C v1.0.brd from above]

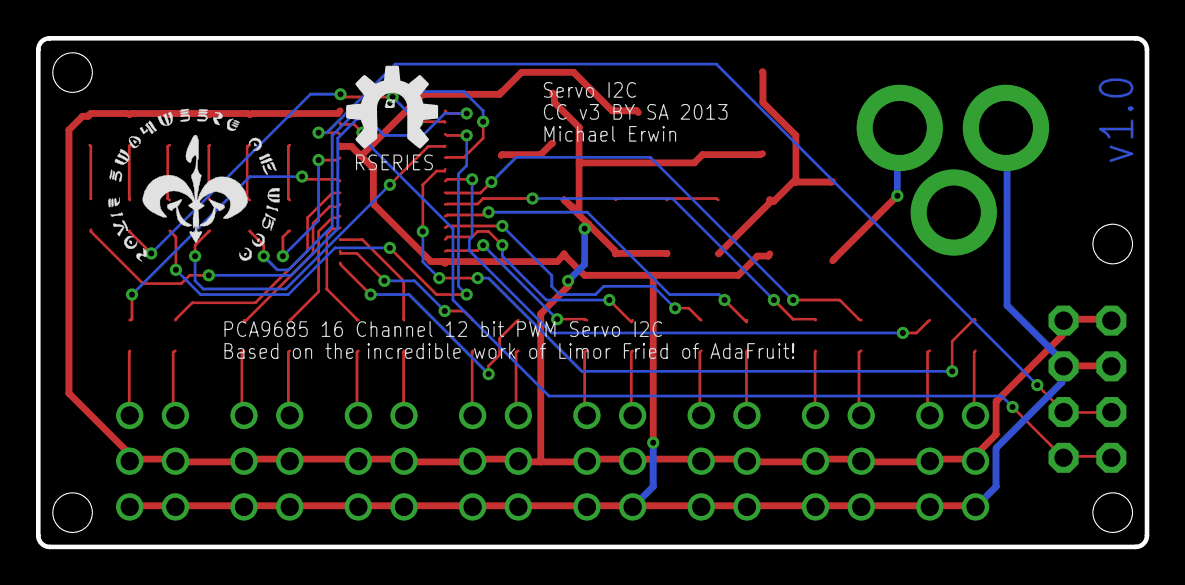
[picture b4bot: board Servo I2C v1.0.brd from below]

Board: 2 copper layers, 61.6 x 28.3 mm, 59 parts (2 on the bottom side), 52 nets.

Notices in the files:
parts and their libraries:
SparkFun-Electromechanical: Licensing: CC v3.0 Share-Alike You are welcome to use this library for commercial purposes.
